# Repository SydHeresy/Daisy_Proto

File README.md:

# Daisy_Proto
Daisy Eurorrack Prototype

#####################################

First attempt at designing a PCB from hacked togehter schematics... What could go wrong?

NOTE: THIS DESIGN IS UNTESTED!!!
I will test it soon and update the files. 

#####################################

Sep-15 2022 Changes

Added DC/DC power block and opAmps for audio input. 
Redesigned PCB completely moving all components to one side so that it can lay flat.

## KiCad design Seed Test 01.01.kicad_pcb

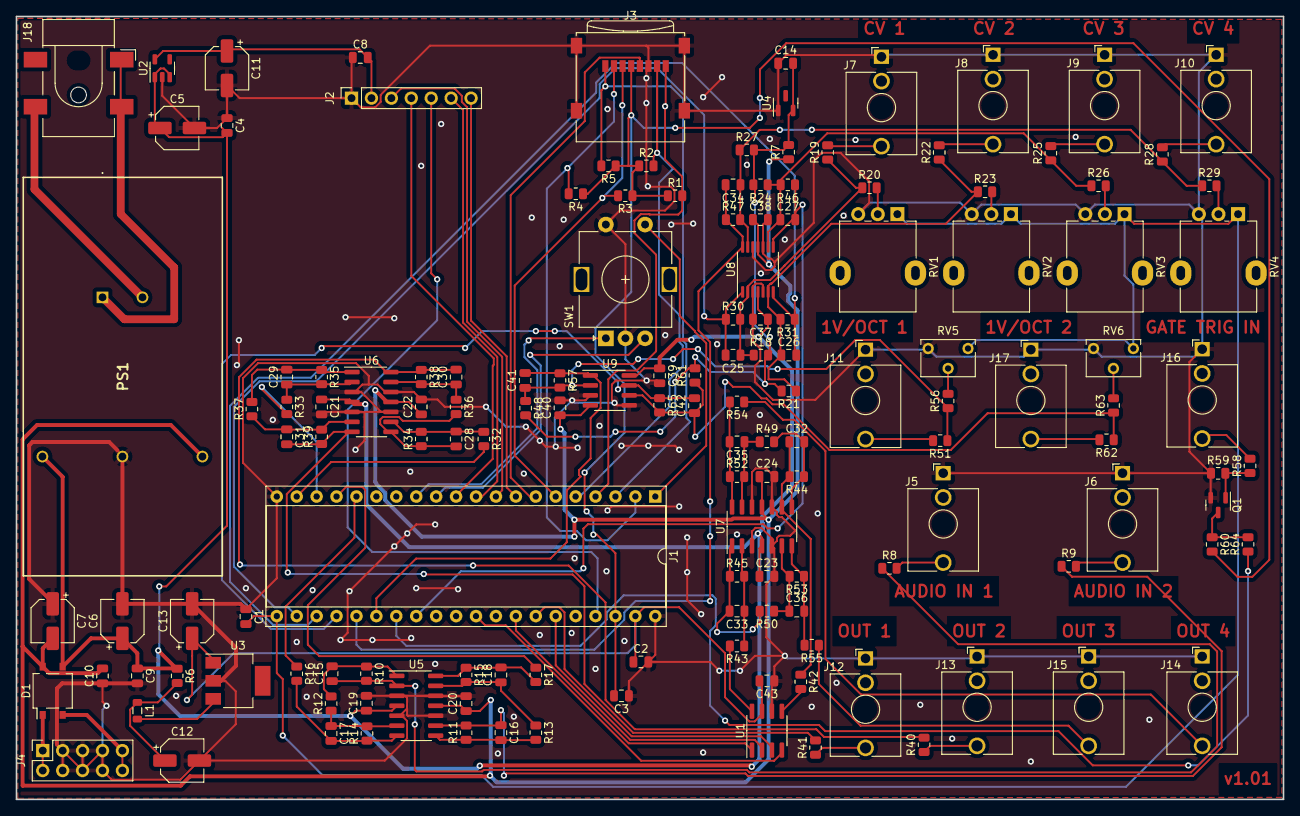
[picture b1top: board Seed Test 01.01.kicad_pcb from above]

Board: 2 copper layers, 161.5 x 99.8 mm, 146 parts (0 on the bottom side), 96 nets.

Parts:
C1, C2, C3, C4, C8, C9, C10, C14, C19, C20, C21, C22, C23, C24, C37, C38, C39, C40, C43: 100nF; C_0805_2012Metric
C5, C6, C7, C11, C12, C13: 10uF; CP_Elec_5x3
C15, C16, C17, C18, C28, C29, C30, C31, C32, C33, C35, C36: 47pF; C_0805_2012Metric
C25, C26, C27, C34, C41, C42: 10nF; C_0805_2012Metric
D1: MB2S; TO-269AA
J1: Daisy_Seed_Temp; DIP-40_W15.24mm_Socket
J2: DISP_3_128X64; PinSocket_1x07_P2.54mm_Vertical
J3: Micro_SD_Card; microSD_HC_Wuerth_693072010801
J4: EURO_PWR; PinSocket_2x05_P2.54mm_Vertical
J5: AUDIO_IN_1L; Jack_3.5mm_QingPu_WQP-PJ398SM_Vertical_CircularHoles
J6: AUDIO_IN_2R; Jack_3.5mm_QingPu_WQP-PJ398SM_Vertical_CircularHoles
J7: CV1_INPUT; Jack_3.5mm_QingPu_WQP-PJ398SM_Vertical_CircularHoles
J8: CV2_INPUT; Jack_3.5mm_QingPu_WQP-PJ398SM_Vertical_CircularHoles
J9: CV3_INPUT; Jack_3.5mm_QingPu_WQP-PJ398SM_Vertical_CircularHoles
J10: CV4_INPUT; Jack_3.5mm_QingPu_WQP-PJ398SM_Vertical_CircularHoles
J11: 1VOCT1_IN; Jack_3.5mm_QingPu_WQP-PJ398SM_Vertical_CircularHoles
J12: MAIN_OUT1; Jack_3.5mm_QingPu_WQP-PJ398SM_Vertical_CircularHoles
J13: MAIN_OUT2; Jack_3.5mm_QingPu_WQP-PJ398SM_Vertical_CircularHoles
J14: MAIN_OUT4; Jack_3.5mm_QingPu_WQP-PJ398SM_Vertical_CircularHoles
J15: MAIN_OUT3; Jack_3.5mm_QingPu_WQP-PJ398SM_Vertical_CircularHoles
J16: GATE_TRIGGER_IN; Jack_3.5mm_QingPu_WQP-PJ398SM_Vertical_CircularHoles
J17: 1VOCT2_IN; Jack_3.5mm_QingPu_WQP-PJ398SM_Vertical_CircularHoles
J18: Barrel_Jack_MountingPin; BarrelJack_CLIFF_FC681465S_SMT_Horizontal
L1: 10uH; L_0805_2012Metric
PS1: DLW05A-12; DLW05A12
Q1: MMBT3904; SOT-23
R1, R2, R3, R4, R5: 47k; R_0805_2012Metric
R6: 4.7R; R_0805_2012Metric
R7: 2k; R_0805_2012Metric
R8, R9, R10, R11, R12, R13, R14, R15, R19, R22, R25, R28, R34, R35, R36, R37, R38, R39, R44, R45, R49, R50, R51, R52, R53, R58, R62: 100k; R_0805_2012Metric
R16, R17, R40, R41, R54, R55, R64: 1k; R_0805_2012Metric
R18, R21, R24, R27, R48, R61: 200k; R_0805_2012Metric
R20, R23, R26, R29, R30, R31, R46, R47, R56, R57, R63, R65: 66.5k; R_0805_2012Metric
R32, R33, R42, R43, R60: 10k; R_0805_2012Metric
R59: 1M; R_0805_2012Metric
RV1: CV_CNTRL_1; Potentiometer_Alpha_RD901F-40-00D_Single_Vertical
RV2: CV_CNTRL_2; Potentiometer_Alpha_RD901F-40-00D_Single_Vertical
RV3: CV_CNTRL_3; Potentiometer_Alpha_RD901F-40-00D_Single_Vertical
RV4: CV_CNTRL_4; Potentiometer_Alpha_RD901F-40-00D_Single_Vertical
RV5, RV6: IN_CAL_TRIM; Potentiometer_Bourns_3266W_Vertical
SW1: RotaryEncoder_Switch; RotaryEncoder_Alps_EC11E-Switch_Vertical_H20mm
U1: CS4334; SOIC-8_3.9x4.9mm_P1.27mm
U2: AP2204K-3.3; SOT-23-5
U3: LM78L05_SOT; SOT-223
U4: LM4040DBZ-10; SOT-23
U5, U6, U7: TL074; SOIC-14_3.9x8.7mm_P1.27mm
U8: MCP6004; TSSOP-14_4.4x5mm_P0.65mm
U9: MCP6002-xSN; SOIC-8_3.9x4.9mm_P1.27mm

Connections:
+3.3VA: C3.2, J1.38, J3.4 (VDD), R1.1, R2.1, R3.1, R4.1, R5.1, R60.2
+3.3VP: C1.2, J1.21, RV1.1, RV2.1, RV3.1, RV4.1, RV5.1, RV6.1
+3V3: C8.2, C11.1, J2.2, U2.5 (VOUT)
+5V: C2.1, C13.1, C43.2, J1.39, U1.7 (VA), U3.1 (VO)
+12V: C4.2, C5.1, C6.1, C9.1, C19.1, C21.1, C23.1, C37.1, C39.1, D1.3 (+), PS1.3 (+VOUT), R6.1, U2.1 (VIN), U2.3 (EN), U5.4 (V+), U6.4 (V+), U7.4 (V+), U8.4 (V+), U9.8 (V+)
-10V: C14.2, R7.2, R18.2, R21.2, R24.2, R27.2, R48.2, R61.2, U4.2 (A)
-12V: C7.2, C10.2, C20.1, C22.1, C24.1, C38.1, C40.1, D1.4 (-), PS1.5 (-VOUT), R7.1, U5.11 (V-), U6.11 (V-), U7.11 (V-), U8.11 (V-), U9.4 (V-)
ADC1_1VOCT1: C41.2, J1.26, R57.1, U9.1
ADC1_1VOCT2: C42.2, J1.24, R65.1, U9.7
ADC1_GATE_IN: J1.27, R64.1
ADC_CTRL_1: C25.2, J1.22, R30.1, U8.1
ADC_CTRL_2: C26.2, J1.23, R31.1, U8.7
ADC_CTRL_3: C27.2, J1.28, R46.1, U8.8
ADC_CTRL_4: C34.2, J1.25, R47.1, U8.14
AUDIO_IN_L: J1.16, R16.1
AUDIO_IN_R: J1.17, R17.1
AUDIO_OUT_L: J1.18, R33.2
AUDIO_OUT_R: J1.19, R32.2
DAC_AUDIO_L: R43.2, U1.8 (AOUTL)
DAC_AUDIO_R: R42.2, U1.5 (AOUTR)
ENC_A: J1.13, SW1.A
ENC_B: J1.12, SW1.B
ENC_CLICK: J1.1, SW1.S1
GNDA: C1.1, C2.2, C3.1, C4.1, C5.2, C6.2, C7.1, C8.1, C9.2, C10.1, C11.2, C12.2, C13.2, C14.1, C19.2, C20.2, C21.2, C22.2, C23.2, C24.2, C37.2, C38.2, C39.2, C40.2, C43.1, J1.20, J1.40, J2.1, J3.6 (VSS), J3.9 (SHIELD), J4.3, J4.4, J4.5, J4.6, J4.7, J4.8, J5.S, J6.S, J7.S, J8.S, J9.S, J10.S, J11.S, J12.S, J13.S, J14.S, J15.S, J16.S, J17.S, PS1.4 (COM), Q1.2 (E), R59.1, RV1.3, RV2.3, RV3.3, RV4.3, RV5.3, RV6.3, SW1.C, SW1.S2, U1.6 (AGND), U2.2 (GND), U3.2 (GND), U4.1 (K), U5.3 (+), U5.5 (+), U5.10 (+), U5.12 (+), U6.3 (+), U6.5 (+), U6.10 (+), U6.12 (+), U7.3 (+), U7.5 (+), U7.10 (+), U7.12 (+), U8.3 (+), U8.5 (+), U8.10 (+), U8.12 (+), U9.3 (+), U9.5 (+)
unnamed: C12.1, L1.1, R6.2
unnamed: C15.1, R8.1, R10.2, U5.2 (-)
unnamed: C15.2, R10.1, R12.2, U5.1
unnamed: C16.1, R9.1, R11.2, U5.9 (-)
unnamed: C16.2, R11.1, R13.2, U5.8
unnamed: C17.1, R12.1, R14.2, U5.6 (-)
unnamed: C17.2, R14.1, R16.2, U5.7
unnamed: C18.1, R13.1, R15.2, U5.13 (-)
unnamed: C18.2, R15.1, R17.2, U5.14
unnamed: C25.1, R18.1, R19.1, R20.1, R30.2, U8.2 (-)
unnamed: C26.1, R21.1, R22.1, R23.1, R31.2, U8.6 (-)
unnamed: C27.1, R24.1, R25.1, R26.1, R46.2, U8.9 (-)
unnamed: C28.1, R32.1, R34.2, U6.9 (-)
unnamed: C28.2, R34.1, R36.2, U6.8
unnamed: C29.1, R33.1, R35.2, U6.2 (-)
unnamed: C29.2, R35.1, R37.2, U6.1
unnamed: C30.1, R36.1, R38.2, U6.13 (-)
unnamed: C30.2, R38.1, R40.2, U6.14
unnamed: C31.1, R37.1, R39.2, U6.6 (-)
unnamed: C31.2, R39.1, R41.2, U6.7
unnamed: C32.1, R42.1, R44.2, U7.9 (-)
unnamed: C32.2, R44.1, R49.2, U7.8
unnamed: C33.1, R43.1, R45.2, U7.2 (-)
unnamed: C33.2, R45.1, R50.2, U7.1
unnamed: C34.1, R27.1, R28.1, R29.1, R47.2, U8.13 (-)
unnamed: C35.1, R49.1, R52.2, U7.13 (-)
unnamed: C35.2, R52.1, R54.2, U7.14
unnamed: C36.1, R50.1, R53.2, U7.6 (-)
unnamed: C36.2, R53.1, R55.2, U7.7
unnamed: C41.1, R48.1, R51.1, R56.1, R57.2, U9.2 (-)
unnamed: C42.1, R61.1, R62.1, R63.1, R65.2, U9.6 (-)
unnamed: J5.T, R8.2
unnamed: J6.T, R9.2
unnamed: J7.T, R19.2
unnamed: J8.T, R22.2
unnamed: J9.T, R25.2
unnamed: J10.T, R28.2
unnamed: J11.T, R51.2
unnamed: J12.T, R41.1
unnamed: J13.T, R40.1
unnamed: J14.T, R54.1
unnamed: J15.T, R55.1
unnamed: J16.T, R58.2
unnamed: J17.T, R62.2
unnamed: J18.1, PS1.1 (+VIN)
unnamed: J18.2, PS1.2 (-VIN)
unnamed: L1.2, U3.3 (VI)
unnamed: Q1.1 (B), R58.1, R59.2
unnamed: Q1.3 (C), R60.1, R64.2
unnamed: R20.2, RV1.2
unnamed: R23.2, RV2.2
unnamed: R26.2, RV3.2
unnamed: R29.2, RV4.2
unnamed: R56.2, RV5.2
unnamed: R63.2, RV6.2
OLED_CMD_MISO: J1.10, J2.6
OLED_CS: J1.8, J2.7
OLED_DATA_MOSI: J1.11, J2.4
OLED_RST: J1.37, J2.5
OLED_SCK: J1.9, J2.3
SAI2_FS_A: J1.34, U1.3 (LRCK)
SAI2_MCLK: J1.31, U1.4 (MCLK)
SAI2_SCK_A: J1.35, U1.2 (~DEM/SCLK)
SAI2_SD_A: J1.33, U1.1 (SDATA)
SDMMC1_CK: J1.7, J3.5 (CLK)
SDMMC1_CMD: J1.6, J3.3 (CMD), R3.2
SDMMC1_D0: J1.5, J3.7 (DAT0), R2.2
SDMMC1_D1: J1.4, J3.8 (DAT1), R1.2
SDMMC1_D2: J1.3, J3.1 (DAT2), R5.2
SDMMC1_D3: J1.2, J3.2 (DAT3/CD), R4.2
VCC: D1.1, J4.1, J4.2
VEE: D1.2, J4.9, J4.10

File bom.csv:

Designator,Footprint,Quantity,Value,LCSC Part #
"C1, C10, C14, C19, C2, C20, C21, C22, C23, C24, C3, C37, C38, C39, C4, C40, C43, C8, C9",C_0805_2012Metric,19,100nF,
"C11, C12, C13, C5, C6, C7",CP_Elec_5x3,6,10uF,
"C15, C16, C17, C18, C28, C29, C30, C31, C32, C33, C35, C36",C_0805_2012Metric,12,47pF,
"C25, C26, C27, C34, C41, C42",C_0805_2012Metric,6,10nF,
D1,TO-269AA,1,MB2S,
J1,DIP-40_W15.24mm_Socket,1,Daisy_Seed_Temp,
J10,Jack_3.5mm_QingPu_WQP-PJ398SM_Vertical_CircularHoles,1,CV4_INPUT,
J11,Jack_3.5mm_QingPu_WQP-PJ398SM_Vertical_CircularHoles,1,1VOCT1_IN,
J12,Jack_3.5mm_QingPu_WQP-PJ398SM_Vertical_CircularHoles,1,MAIN_OUT1,
J13,Jack_3.5mm_QingPu_WQP-PJ398SM_Vertical_CircularHoles,1,MAIN_OUT2,
J14,Jack_3.5mm_QingPu_WQP-PJ398SM_Vertical_CircularHoles,1,MAIN_OUT4,
J15,Jack_3.5mm_QingPu_WQP-PJ398SM_Vertical_CircularHoles,1,MAIN_OUT3,
J16,Jack_3.5mm_QingPu_WQP-PJ398SM_Vertical_CircularHoles,1,GATE_TRIGGER_IN,
J17,Jack_3.5mm_QingPu_WQP-PJ398SM_Vertical_CircularHoles,1,1VOCT2_IN,
J18,BarrelJack_CLIFF_FC681465S_SMT_Horizontal,1,Barrel_Jack_MountingPin,
J2,PinSocket_1x07_P2.54mm_Vertical,1,DISP_3_128X64,
J3,microSD_HC_Wuerth_693072010801,1,Micro_SD_Card,
J4,PinSocket_2x05_P2.54mm_Vertical,1,EURO_PWR,
J5,Jack_3.5mm_QingPu_WQP-PJ398SM_Vertical_CircularHoles,1,AUDIO_IN_1L,
J6,Jack_3.5mm_QingPu_WQP-PJ398SM_Vertical_CircularHoles,1,AUDIO_IN_2R,
J7,Jack_3.5mm_QingPu_WQP-PJ398SM_Vertical_CircularHoles,1,CV1_INPUT,
J8,Jack_3.5mm_QingPu_WQP-PJ398SM_Vertical_CircularHoles,1,CV2_INPUT,
J9,Jack_3.5mm_QingPu_WQP-PJ398SM_Vertical_CircularHoles,1,CV3_INPUT,
L1,L_0805_2012Metric,1,10uH,
PS1,DLW05A12,1,DLW05A-12,
Q1,SOT-23,1,MMBT3904,
"R1, R2, R3, R4, R5",R_0805_2012Metric,5,47k,
"R10, R11, R12, R13, R14, R15, R19, R22, R25, R28, R34, R35, R36, R37, R38, R39, R44, R45, R49, R50, R51, R52, R53, R58, R62, R8, R9",R_0805_2012Metric,27,100k,
"R16, R17, R40, R41, R54, R55, R64",R_0805_2012Metric,7,1k,
"R18, R21, R24, R27, R48, R61",R_0805_2012Metric,6,200k,
"R20, R23, R26, R29, R30, R31, R46, R47, R56, R57, R63, R65",R_0805_2012Metric,12,66.5k,
"R32, R33, R42, R43, R60",R_0805_2012Metric,5,10k,
R59,R_0805_2012Metric,1,1M,
"R6, R7",R_0805_2012Metric,2,4.7R,
RV1,Potentiometer_Alpha_RD901F-40-00D_Single_Vertical,1,CV_CNTRL_1,
RV2,Potentiometer_Alpha_RD901F-40-00D_Single_Vertical,1,CV_CNTRL_2,
RV3,Potentiometer_Alpha_RD901F-40-00D_Single_Vertical,1,CV_CNTRL_3,
RV4,Potentiometer_Alpha_RD901F-40-00D_Single_Vertical,1,CV_CNTRL_4,
"RV5, RV6",Potentiometer_Bourns_3266W_Vertical,2,IN_CAL_TRIM,
SW1,RotaryEncoder_Alps_EC11E-Switch_Vertical_H20mm,1,RotaryEncoder_Switch,
U1,SOIC-8_3.9x4.9mm_P1.27mm,1,CS4334,
U2,SOT-23-5,1,AP2204K-3.3,
U3,SOT-223,1,LM1117-5.0,
U4,SOT-23,1,LM4040DBZ-5,
"U5, U6, U7",SOIC-14_3.9x8.7mm_P1.27mm,3,TL074,
U8,TSSOP-14_4.4x5mm_P0.65mm,1,MCP6004,
U9,SOIC-8_3.9x4.9mm_P1.27mm,1,MCP6002-xSN,

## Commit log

2022-08-30 updated power rails error
2022-08-30 removed old files
2022-09-15 Version update
    Added DC/DC power block and opAmps for audio input. Redesigned PCB completely moving all components to one side so that it can lay flat.
2022-09-18 Gerber files, BOM updated
    Added Gerber files, updated the BOM, and fixed the power sheet to have the correct file name.
2022-10-28 PCB rev 1.0
    PCB finished layout in 0805
2022-10-29 added PDF board and schematics
    updated with PDF board and schematics
2023-04-19 various updates
